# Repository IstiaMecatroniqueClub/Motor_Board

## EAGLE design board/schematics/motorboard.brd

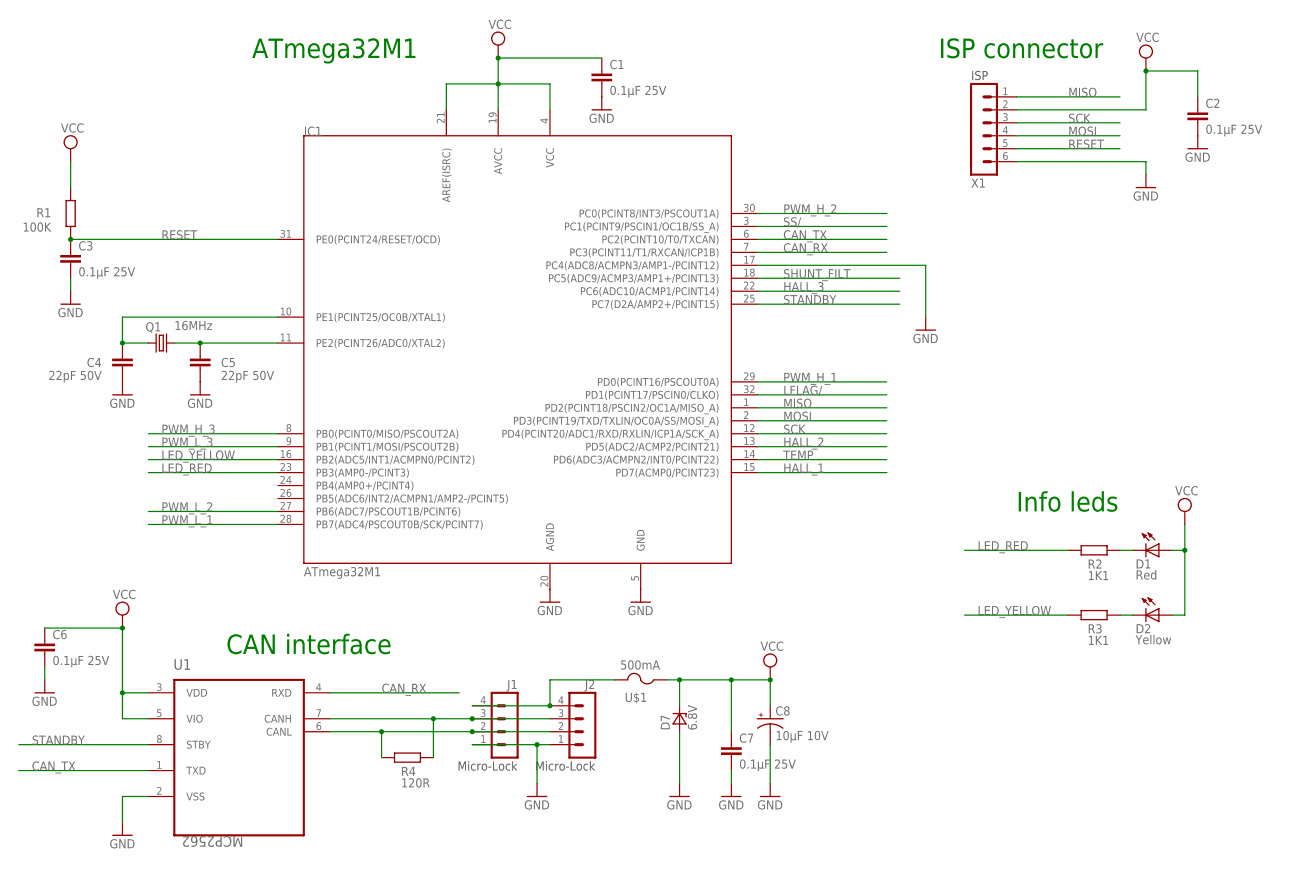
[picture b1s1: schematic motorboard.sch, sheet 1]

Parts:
C1, C2, C3, C6, C7: 0.1µF 25V; C2012
C4, C5: 22pF 50V; C2012
C8: 10µF 10V; EIA3216
D1: Red; VLD
D2: Yellow; VLD
D7: 6.8V; DO-214AA
IC1: ATmega32M1; TQFP32
J1, J2: Micro-Lock; 504195-0470
Q1: 16MHz; SMD_KX7
R1: 100K; R2012
R2, R3: 1K1; R2012
R4: 120R; R2012
U1: MCP2562; SOIC8
U$1: 500mA; EIARS-481-2
X1: ISP; MINITEK_127_6WAY_SMD

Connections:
CAN_RX: IC1.7 (PC3(PCINT11/T1/RXCAN/ICP1B)), U1.4 (RXD)
CAN_TX: IC1.6 (PC2(PCINT10/T0/TXCAN)), U1.1 (TXD)
GND: C1.2, C2.2, C3.2, C4.2, C5.2, C6.2, C7.2, C8.C (-), D7.A, IC1.5 (GND), IC1.17 (PC4(ADC8/ACMPN3/AMP1-/PCINT12)), IC1.20 (AGND), J1.1, J2.1, U1.2 (VSS), X1.6; also elsewhere on the board
HALL_1: IC1.15 (PD7(ACMP0/PCINT23)); also elsewhere on the board
HALL_2: IC1.13 (PD5(ADC2/ACMP2/PCINT21)); also elsewhere on the board
HALL_3: IC1.22 (PC6(ADC10/ACMP1/PCINT14)); also elsewhere on the board
LED_RED: IC1.23 (PB3(AMP0-/PCINT3)), R2.2
LED_YELLOW: IC1.16 (PB2(ADC5/INT1/ACMPN0/PCINT2)), R3.2
LFLAG/: IC1.32 (PD1(PCINT17/PSCIN0/CLKO)); also elsewhere on the board
MISO: IC1.1 (PD2(PCINT18/PSCIN2/OC1A/MISO_A)), X1.1; also elsewhere on the board
MOSI: IC1.2 (PD3(PCINT19/TXD/TXLIN/OC0A/SS/MOSI_A)), X1.4; also elsewhere on the board
unnamed: D1.C, R2.1
unnamed: D2.C, R3.1
unnamed: J1.4, J2.4, U$1.2
unnamed: J1.2, J2.2, R4.2, U1.6 (CANL)
unnamed: J1.3, J2.3, R4.1, U1.7 (CANH)
unnamed: C5.1, IC1.11 (PE2(PCINT26/ADC0/XTAL2)), Q1.3 (2)
unnamed: C4.1, IC1.10 (PE1(PCINT25/OC0B/XTAL1)), Q1.1
PWM_H_1: IC1.29 (PD0(PCINT16/PSCOUT0A)); also elsewhere on the board
PWM_H_2: IC1.30 (PC0(PCINT8/INT3/PSCOUT1A)); also elsewhere on the board
PWM_H_3: IC1.8 (PB0(PCINT0/MISO/PSCOUT2A)); also elsewhere on the board
PWM_L_1: IC1.28 (PB7(ADC4/PSCOUT0B/SCK/PCINT7)); also elsewhere on the board
PWM_L_2: IC1.27 (PB6(ADC7/PSCOUT1B/PCINT6)); also elsewhere on the board
PWM_L_3: IC1.9 (PB1(PCINT1/MOSI/PSCOUT2B)); also elsewhere on the board
RESET: C3.1, IC1.31 (PE0(PCINT24/RESET/OCD)), R1.1, X1.5
SCK: IC1.12 (PD4(PCINT20/ADC1/RXD/RXLIN/ICP1A/SCK_A)), X1.3; also elsewhere on the board
SHUNT_FILT: IC1.18 (PC5(ADC9/ACMP3/AMP1+/PCINT13)); also elsewhere on the board
SS/: IC1.3 (PC1(PCINT9/PSCIN1/OC1B/SS_A)); also elsewhere on the board
STANDBY: IC1.25 (PC7(D2A/AMP2+/PCINT15)), U1.8 (STBY); also elsewhere on the board
TEMP: IC1.14 (PD6(ADC3/ACMPN2/INT0/PCINT22)); also elsewhere on the board
VCC: C1.1, C2.1, C6.1, C7.1, C8.A (+), D1.A, D2.A, D7.C, IC1.4 (VCC), IC1.19 (AVCC), IC1.21 (AREF(ISRC)), R1.2, U1.3 (VDD), U1.5 (VIO), U$1.1, X1.2; also elsewhere on the board

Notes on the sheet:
ISP connector
Info leds
CAN interface
ATmega32M1

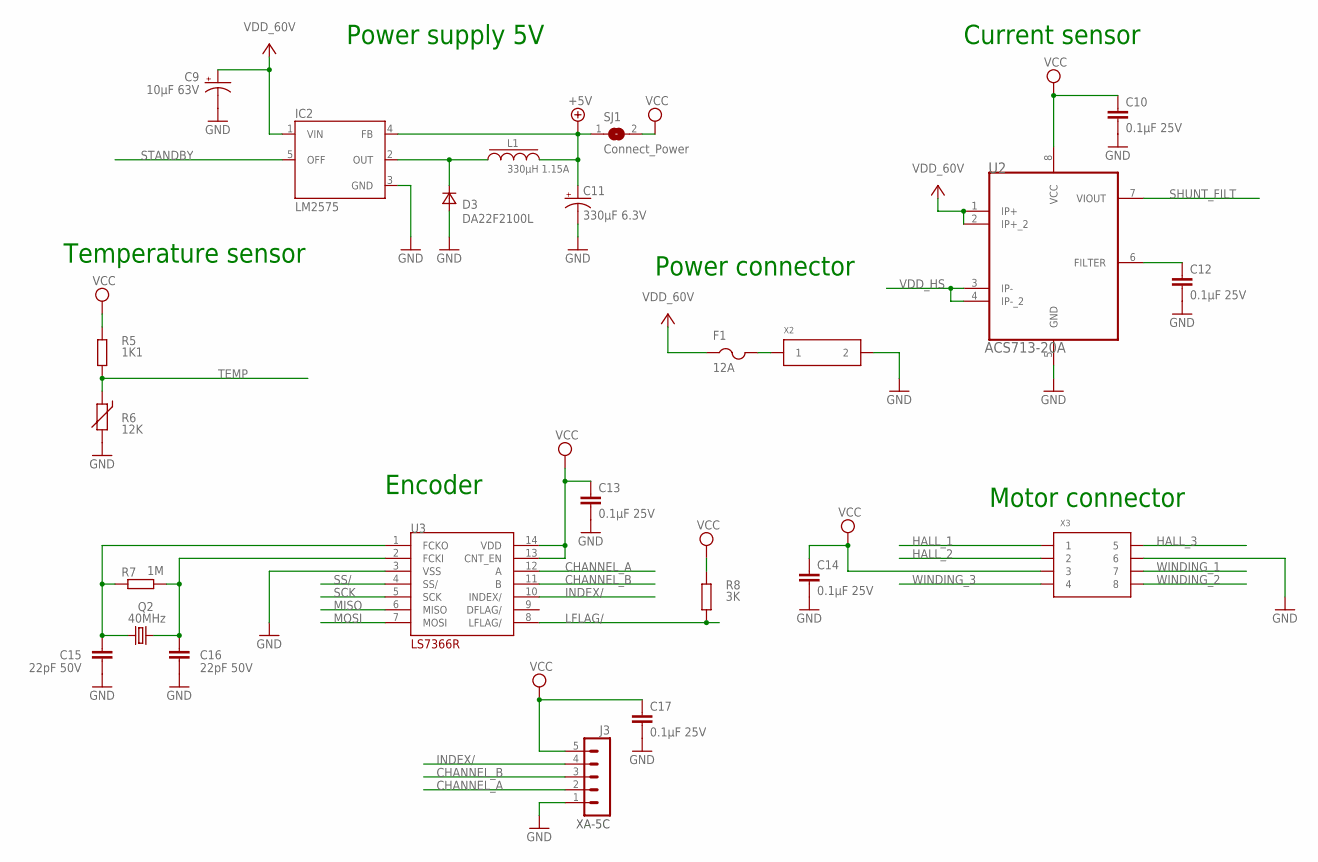
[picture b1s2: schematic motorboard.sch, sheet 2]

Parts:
C9: 10µF 63V; 153CLV-1010
C10, C12, C13, C14, C17: 0.1µF 25V; C2012
C11: 330µF 6.3V; EIA7343
C15, C16: 22pF 50V; C2012
D3: DA22F2100L; SOD323
F1: 12A; R3216
IC2: LM2575; TO263-5
J3: XA-5C; S05B-XASK-1
L1: 330µH 1.15A; DRA124
Q2: 40MHz; SMD_KX7
R5: 1K1; R2012
R6: 12K; T2012
R7: 1M; R2012
R8: 3K; R2012
SJ1: Connect_Power; SJ
U2: ACS713-20A; SOIC8
U3: LS7366R; TSSOP14
X2: Mini-Fit; 5569-02
X3: Mini-Fit; 5569-08

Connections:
+5V: C11.A (+), IC2.4 (FB), L1.2, SJ1.1; also elsewhere on the board
CHANNEL_A: J3.2, U3.12 (A)
CHANNEL_B: J3.3, U3.11 (B)
GND: C9.-, C10.2, C11.C (-), C12.2, C13.2, C14.2, C15.2, C16.2, C17.2, D3.2 (A), IC2.3 (GND), J3.1, R6.2, U2.5 (GND), U3.3 (VSS), X2.P2 (2), X3.P6 (6); also elsewhere on the board
HALL_1: X3.P1 (1); also elsewhere on the board
HALL_2: X3.P2 (2); also elsewhere on the board
HALL_3: X3.P5 (5); also elsewhere on the board
INDEX/: J3.4, U3.10 (INDEX/)
LFLAG/: R8.2, U3.8 (LFLAG/); also elsewhere on the board
MISO: U3.6 (MISO); also elsewhere on the board
MOSI: U3.7 (MOSI); also elsewhere on the board
unnamed: D3.1 (C), IC2.2 (OUT), L1.1
unnamed: C16.1, Q2.3 (2), R7.2, U3.2 (FCKI)
unnamed: C15.1, Q2.1, R7.1, U3.1 (FCKO)
unnamed: F1.2, X2.P1 (1)
unnamed: C12.1, U2.6 (FILTER)
SCK: U3.5 (SCK); also elsewhere on the board
SHUNT_FILT: U2.7 (VIOUT); also elsewhere on the board
SS/: U3.4 (SS/); also elsewhere on the board
STANDBY: IC2.5 (OFF); also elsewhere on the board
TEMP: R5.1, R6.1; also elsewhere on the board
VCC: C10.1, C13.1, C14.1, C17.1, J3.5, R5.2, R8.1, SJ1.2, U2.8 (VCC), U3.13 (CNT_EN), U3.14 (VDD), X3.P3 (3); also elsewhere on the board
VDD: C9.+, F1.1, IC2.1 (VIN), U2.1 (IP+), U2.2 (IP+_2)
VDD_HS: U2.3 (IP-), U2.4 (IP-_2); also elsewhere on the board
WINDING_1: X3.P7 (7); also elsewhere on the board
WINDING_2: X3.P8 (8); also elsewhere on the board
WINDING_3: X3.P4 (4); also elsewhere on the board

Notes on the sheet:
Current sensor
Power supply 5V
Motor connector
Encoder
Power connector
Temperature sensor

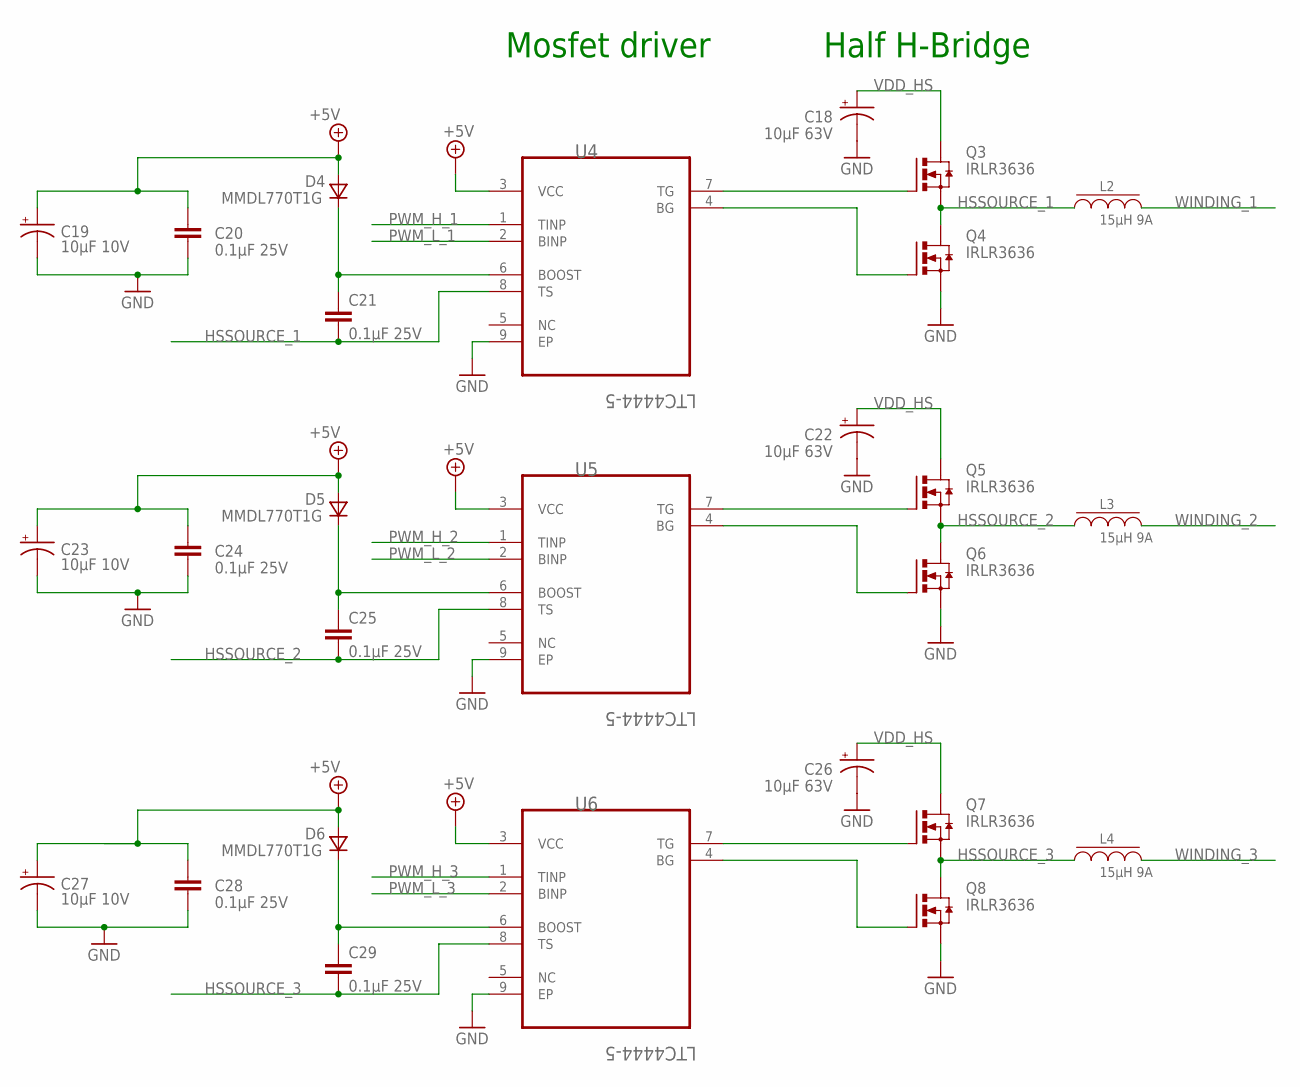
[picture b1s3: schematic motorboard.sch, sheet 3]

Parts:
C18, C22, C26: 10µF 63V; 153CLV-1010
C19, C23, C27: 10µF 10V; EIA3216
C20, C21, C24, C25, C28, C29: 0.1µF 25V; C2012
D4, D5, D6: MMDL770T1G; SOD323
L2, L3, L4: 15µH 9A; DRA127
Q3, Q4, Q5, Q6, Q7, Q8: IRLR3636; TO252
U4, U5, U6: LTC4444-5; MSOP8

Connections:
+5V: C19.A (+), C20.1, C23.A (+), C24.1, C27.A (+), C28.1, D4.2 (A), D5.2 (A), D6.2 (A), U4.3 (VCC), U5.3 (VCC), U6.3 (VCC); also elsewhere on the board
GND: C18.-, C19.C (-), C20.2, C22.-, C23.C (-), C24.2, C26.-, C27.C (-), C28.2, Q4.3 (S), Q6.3 (S), Q8.3 (S), U4.9 (EP), U5.9 (EP), U6.9 (EP); also elsewhere on the board
HSSOURCE_1: C21.2, L2.1, Q3.3 (S), Q4.4 (D), U4.8 (TS)
HSSOURCE_2: C25.2, L3.1, Q5.3 (S), Q6.4 (D), U5.8 (TS)
HSSOURCE_3: C29.2, L4.1, Q7.3 (S), Q8.4 (D), U6.8 (TS)
unnamed: C25.1, D5.1 (C), U5.6 (BOOST)
unnamed: C21.1, D4.1 (C), U4.6 (BOOST)
unnamed: Q4.1 (G), U4.4 (BG)
unnamed: Q3.1 (G), U4.7 (TG)
unnamed: Q6.1 (G), U5.4 (BG)
unnamed: Q5.1 (G), U5.7 (TG)
unnamed: C29.1, D6.1 (C), U6.6 (BOOST)
unnamed: Q8.1 (G), U6.4 (BG)
unnamed: Q7.1 (G), U6.7 (TG)
PWM_H_1: U4.1 (TINP); also elsewhere on the board
PWM_H_2: U5.1 (TINP); also elsewhere on the board
PWM_H_3: U6.1 (TINP); also elsewhere on the board
PWM_L_1: U4.2 (BINP); also elsewhere on the board
PWM_L_2: U5.2 (BINP); also elsewhere on the board
PWM_L_3: U6.2 (BINP); also elsewhere on the board
VDD_HS: C18.+, C22.+, C26.+, Q3.4 (D), Q5.4 (D), Q7.4 (D); also elsewhere on the board
WINDING_1: L2.2; also elsewhere on the board
WINDING_2: L3.2; also elsewhere on the board
WINDING_3: L4.2; also elsewhere on the board

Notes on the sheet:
Mosfet driver
Half H-Bridge

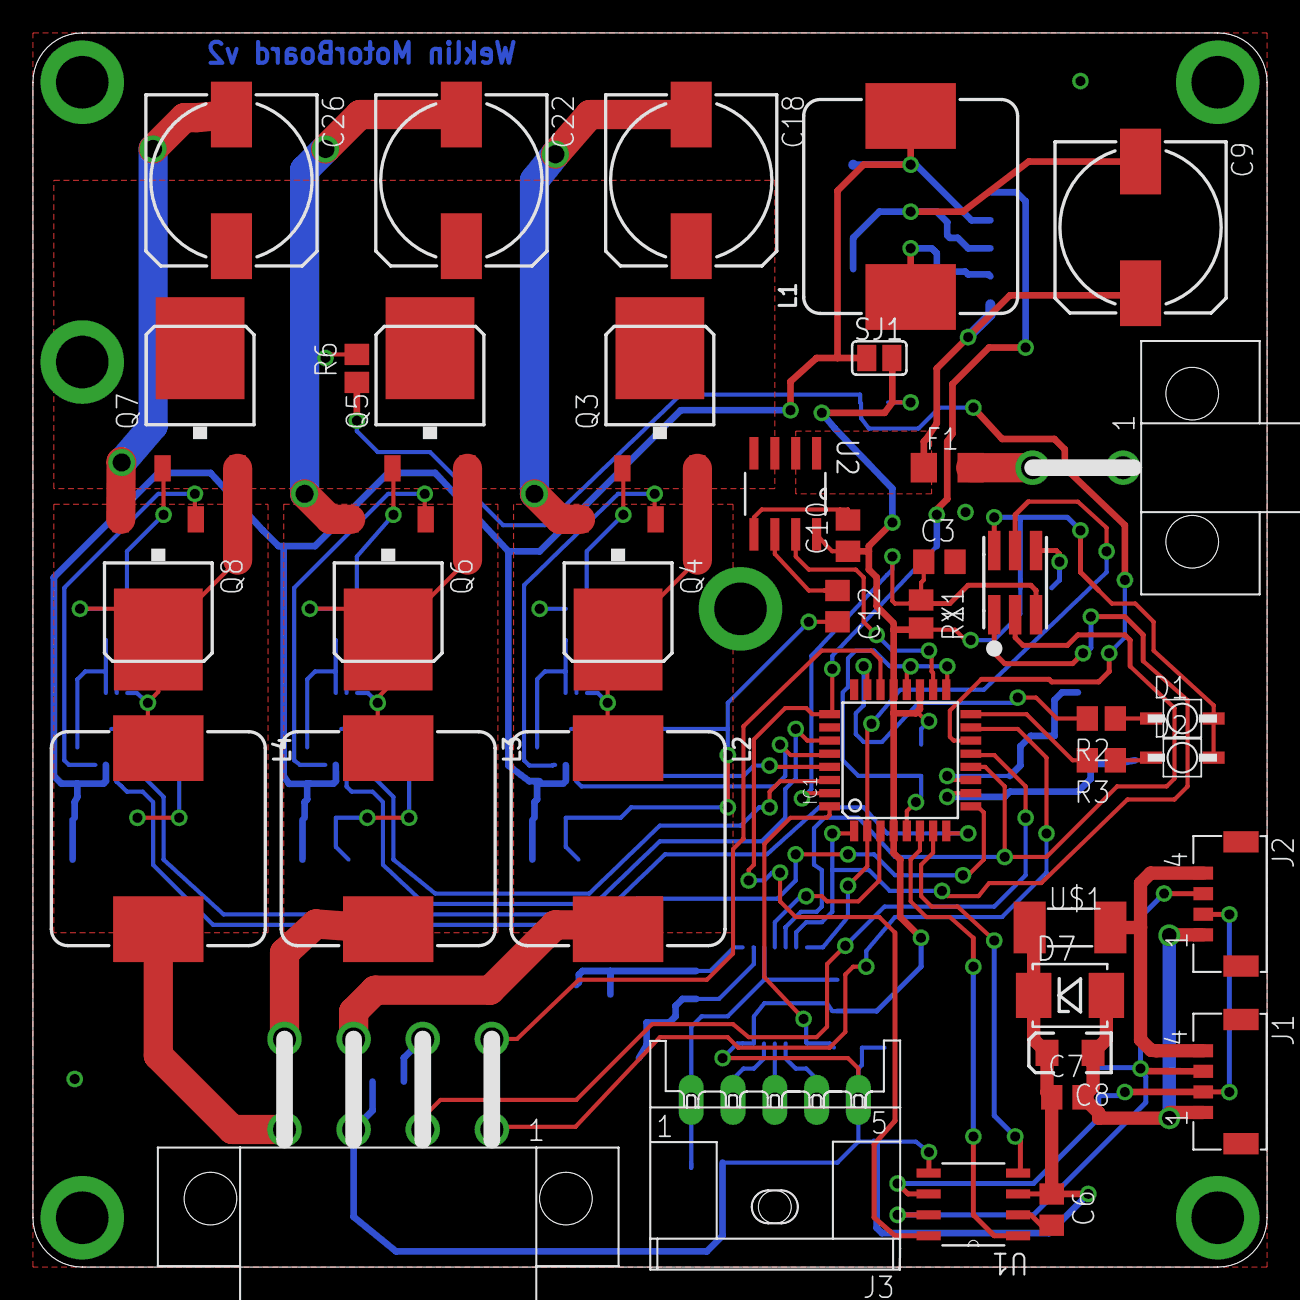
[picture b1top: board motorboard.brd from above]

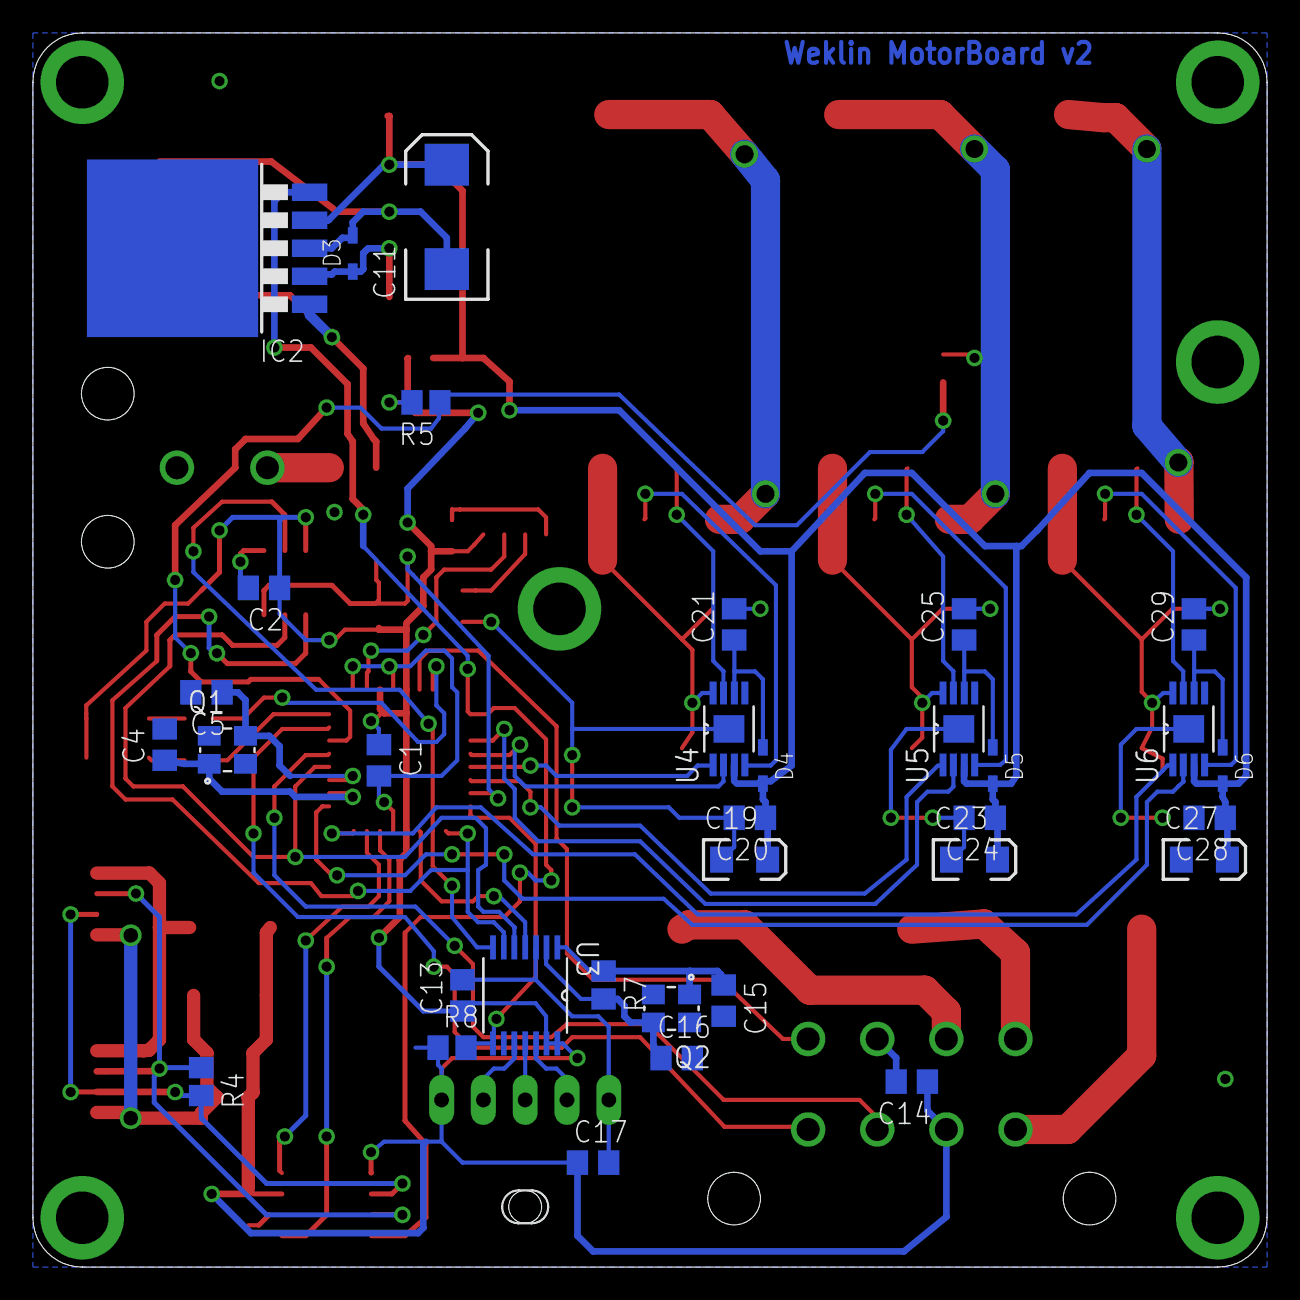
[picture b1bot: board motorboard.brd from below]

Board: 4 copper layers, 74.9 x 74.9 mm, 73 parts (34 on the bottom side), 57 nets.

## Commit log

2017-06-15 Adding source code and schematics
2017-06-23 simple case, without watchdog and pid
2017-06-23 adding watch dog
2017-06-23 removing the test led blinking...
2017-06-23 LSB MSB issue
2017-09-18 Ajout lib CanISR, simplification du code, fonctionnement PID on par defaut
2017-09-18 Activation du pid par defaut
